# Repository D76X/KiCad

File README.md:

# KiCad: ESP32 IoT 4-layer PCB

[KiCad 9: Design & assemble an ESP32 IoT 4-layer PCB loaded with goodies **A Complete Guide** Tech Explorations](https://www.youtube.com/watch?v=LO9AO0XTX3M)  

[Peter Dalmaris futureshocked : KLP-5e-ESP32-sensor-board](https://github.com/futureshocked/KLP-5e-ESP32-sensor-board)  

## Suggested Routing Plan for a 4-layer board

1. Copper zones for GND
2. Copper zones for power
3. Differential pairs
4. Clock and high-speed signals
5. Power traces
6. All other signals
7. Optimization

---

## Parts

[SS-52400-002 Stewart Connector USB Type-C Connector | USB 3.1 | 1 Port | Right Angle Receptacle | Shielded | 0.039 in (1.00mm) PCB Thickness](https://www.snapeda.com/parts/SS-52400-002/Stewart%20Connector/view-part/?ref=search&t=SS-52400-002&ab_test_case=b)  

[MCP73871-2CAI/ML Microchip MCP73871-2CAI/ML, Battery Charge Controller, 1000mA, 20-Pin QFN | Microchip Technology Inc. MCP73871-2CAI/ML](https://www.snapeda.com/parts/MCP73871-2CAI/ML/Microchip/view-part/?ref=search&t=MCP7387-&ab_test_case=b)  

[LM1117MPX-3.3 800-mA 15-V linear voltage regulator](https://www.snapeda.com/parts/LM1117MPX-3.3/Texas%20Instruments/view-part/?ref=search&t=LM1117MPX-3.3&ab_test_case=b)  

[B2B-PH-SM4-TB Connector Header Surface Mount 2 position 0.079" (2.00mm)](https://www.snapeda.com/parts/B2B-PH-SM4-TB/JST/view-part/?ref=search&t=B2B&ab_test_case=b)  

---

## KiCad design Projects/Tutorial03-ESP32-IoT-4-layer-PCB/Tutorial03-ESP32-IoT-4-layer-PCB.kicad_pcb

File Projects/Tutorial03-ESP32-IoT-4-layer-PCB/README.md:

# KiCad

LED6
footprint: Project-Footprints:LEDC2012X120N

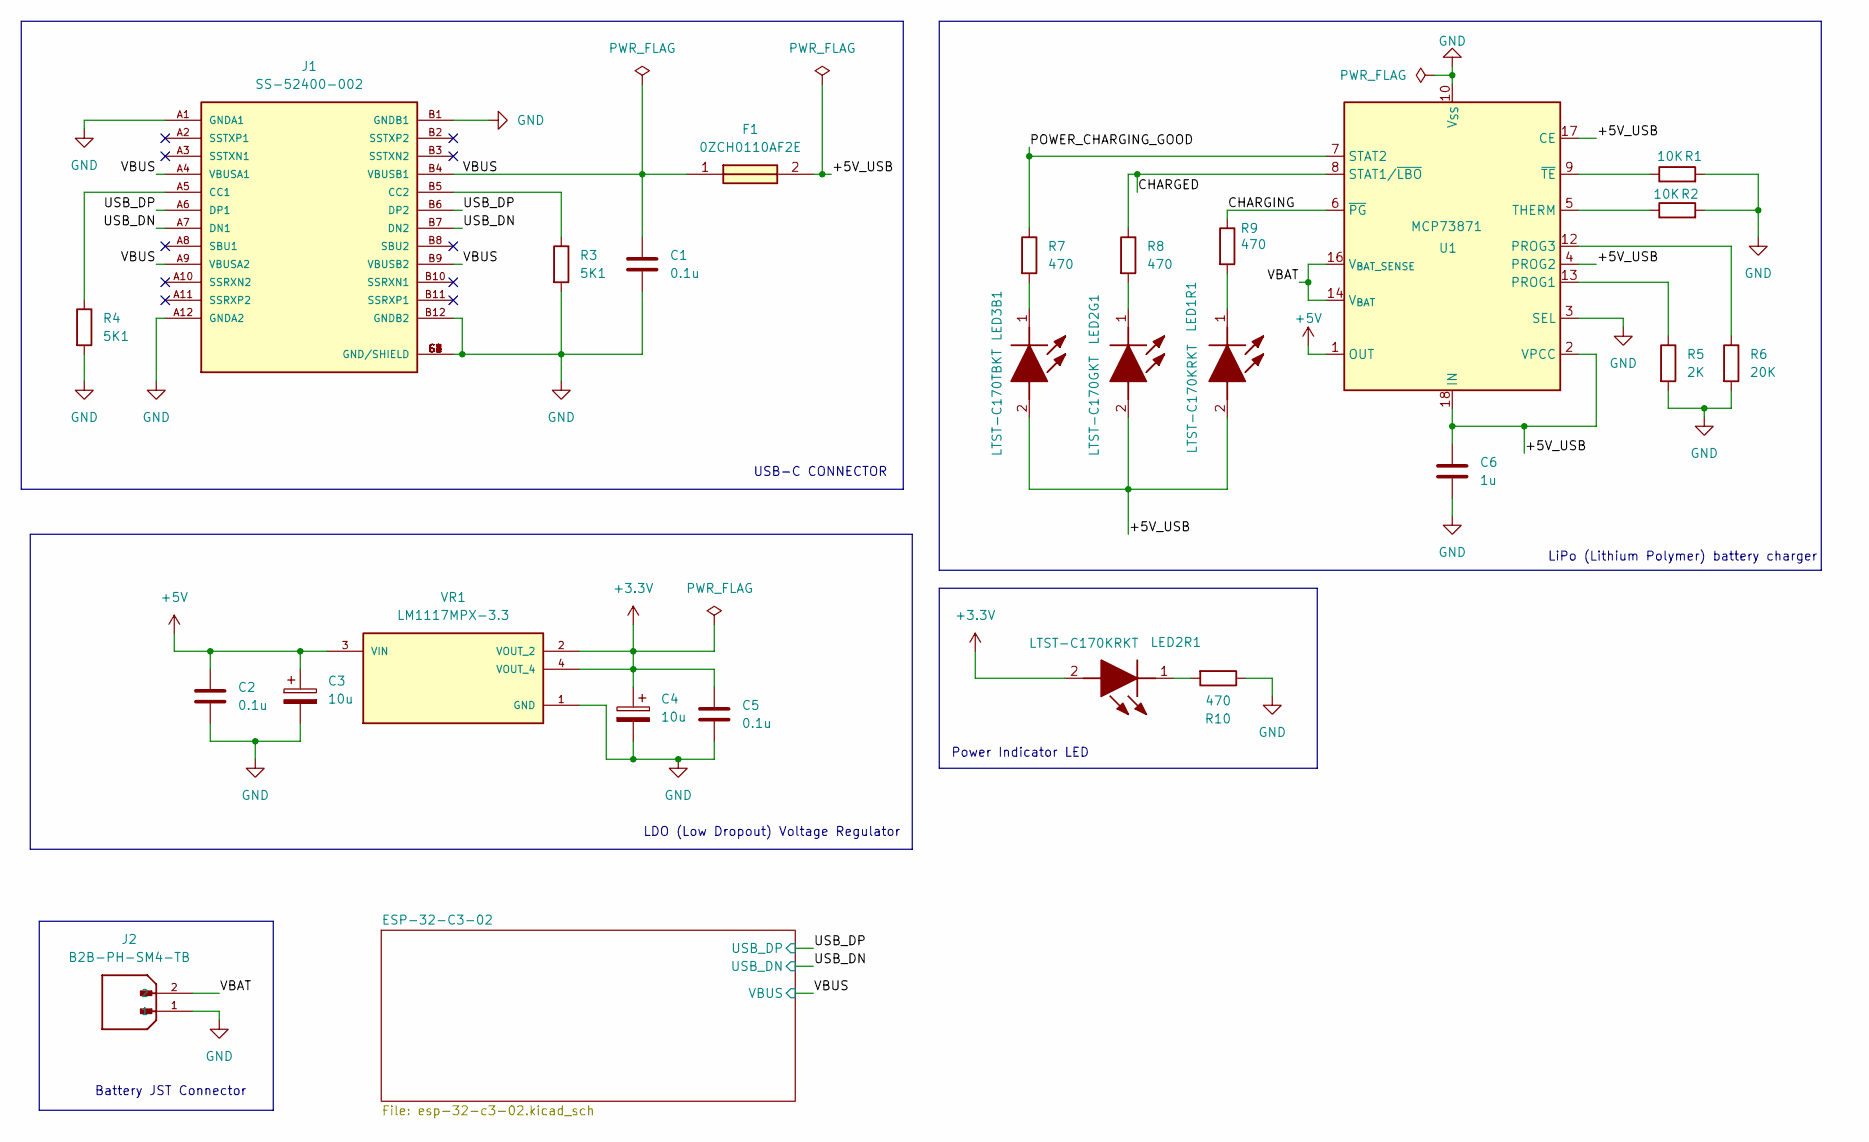
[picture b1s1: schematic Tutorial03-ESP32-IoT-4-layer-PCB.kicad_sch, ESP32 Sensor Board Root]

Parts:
C1, C2, C5: 0.1u; C_0805_2012Metric
C3, C4: 10u; T491A
C6: 1u; C_0805_2012Metric
F1: 0ZCH0110AF2E; FUSC3226X100N; Manufacturer_Part_Number 0ZCH0110AF2E
J1: SS-52400-002; BELFUSE_SS-52400-002; PARTREV A0
J2: B2B-PH-SM4-TB; JST_B2B-PH-SM4-TB; PARTREV N/A
LED1R1, LED2R1: LTST-C170KRKT; LEDC2012X120N; Manufacturer_Part_Number LTST-C170KRKT; Mouser Part Number 859-LTST-C170KRKT
LED2G1: LTST-C170GKT; LEDC2012X120N; Manufacturer_Part_Number LTST-C170GKT; Mouser Part Number 859-LTST-C170GKT
LED3B1: LTST-C170TBKT; LEDC2012X120N; Manufacturer_Part_Number LTST-C170TBKT; Mouser Part Number 859-LTST-C170TBKT
R1, R2: 10K; R_0805_2012Metric
R3, R4: 5K1; R_0805_2012Metric
R5: 2K; R_0805_2012Metric
R6: 20K; R_0805_2012Metric
R7, R8, R9, R10: 470; R_0805_2012Metric
U1: MCP73871; QFN-20-1EP_4x4mm_P0.5mm_EP2.5x2.5mm
VR1: LM1117MPX-3.3; VREG_LM1117MPX-3.3

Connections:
+3.3V: C4.1, C5.1, LED2R1.2 (A), VR1.2 (VOUT_2), VR1.4 (VOUT_4); also elsewhere on the board
+5V: C2.1, C3.1, U1.1 (OUT), U1.20 (OUT), VR1.3 (VIN)
/+5V_USB: C6.1, F1.2, LED1R1.2 (A), LED2G1.2 (A), LED3B1.2 (A), U1.2 (VPCC), U1.4 (PROG2), U1.17 (CE), U1.18 (IN), U1.19 (IN)
/CHARGED: R8.1, U1.8 (STAT1/~LBO)
/CHARGING: R9.1, U1.6 (~PG)
/POWER_CHARGING_GOOD: R7.1, U1.7 (STAT2)
/USB_DN: J1.A7 (DN1), J1.B7 (DN2); also elsewhere on the board
/USB_DP: J1.A6 (DP1), J1.B6 (DP2); also elsewhere on the board
/VBAT: J2.2, U1.14 (V_{BAT}), U1.15 (V_{BAT}), U1.16 (V_{BAT_SENSE})
/VBUS: C1.1, F1.1, J1.A4 (VBUSA1), J1.A9 (VBUSA2), J1.B4 (VBUSB1), J1.B9 (VBUSB2); also elsewhere on the board
GND: C1.2, C2.2, C3.2, C4.2, C5.2, C6.2, J1.A1 (GNDA1), J1.A12 (GNDA2), J1.B1 (GNDB1), J1.B12 (GNDB2), J1.G1 (GND/SHIELD), J1.G2 (GND/SHIELD), J1.G3 (GND/SHIELD), J1.G4 (GND/SHIELD), J1.S1 (GND/SHIELD), J1.S2 (GND/SHIELD), J1.S3 (GND/SHIELD), J1.S4 (GND/SHIELD), J2.1, R1.2, R2.2, R3.2, R4.2, R5.2, R6.2, R10.1, U1.3 (SEL), U1.10 (V_{SS}), U1.11 (V_{SS}), U1.21 (V_{SS}), VR1.1 (GND); also elsewhere on the board
unnamed: J1.A5 (CC1), R4.1
unnamed: J1.B5 (CC2), R3.1
unnamed: LED1R1.1 (K), R9.2
unnamed: LED2G1.1 (K), R8.2
unnamed: LED2R1.1 (K), R10.2
unnamed: LED3B1.1 (K), R7.2
unnamed: R5.1, U1.13 (PROG1)
unnamed: R6.1, U1.12 (PROG3)
unnamed: R2.1, U1.5 (THERM)
unnamed: R1.1, U1.9 (~TE)

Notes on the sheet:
USB-C CONNECTOR
Power Indicator LED
LiPo (Lithium Polymer) battery charger
LDO (Low Dropout) Voltage Regulator
Battery JST Connector

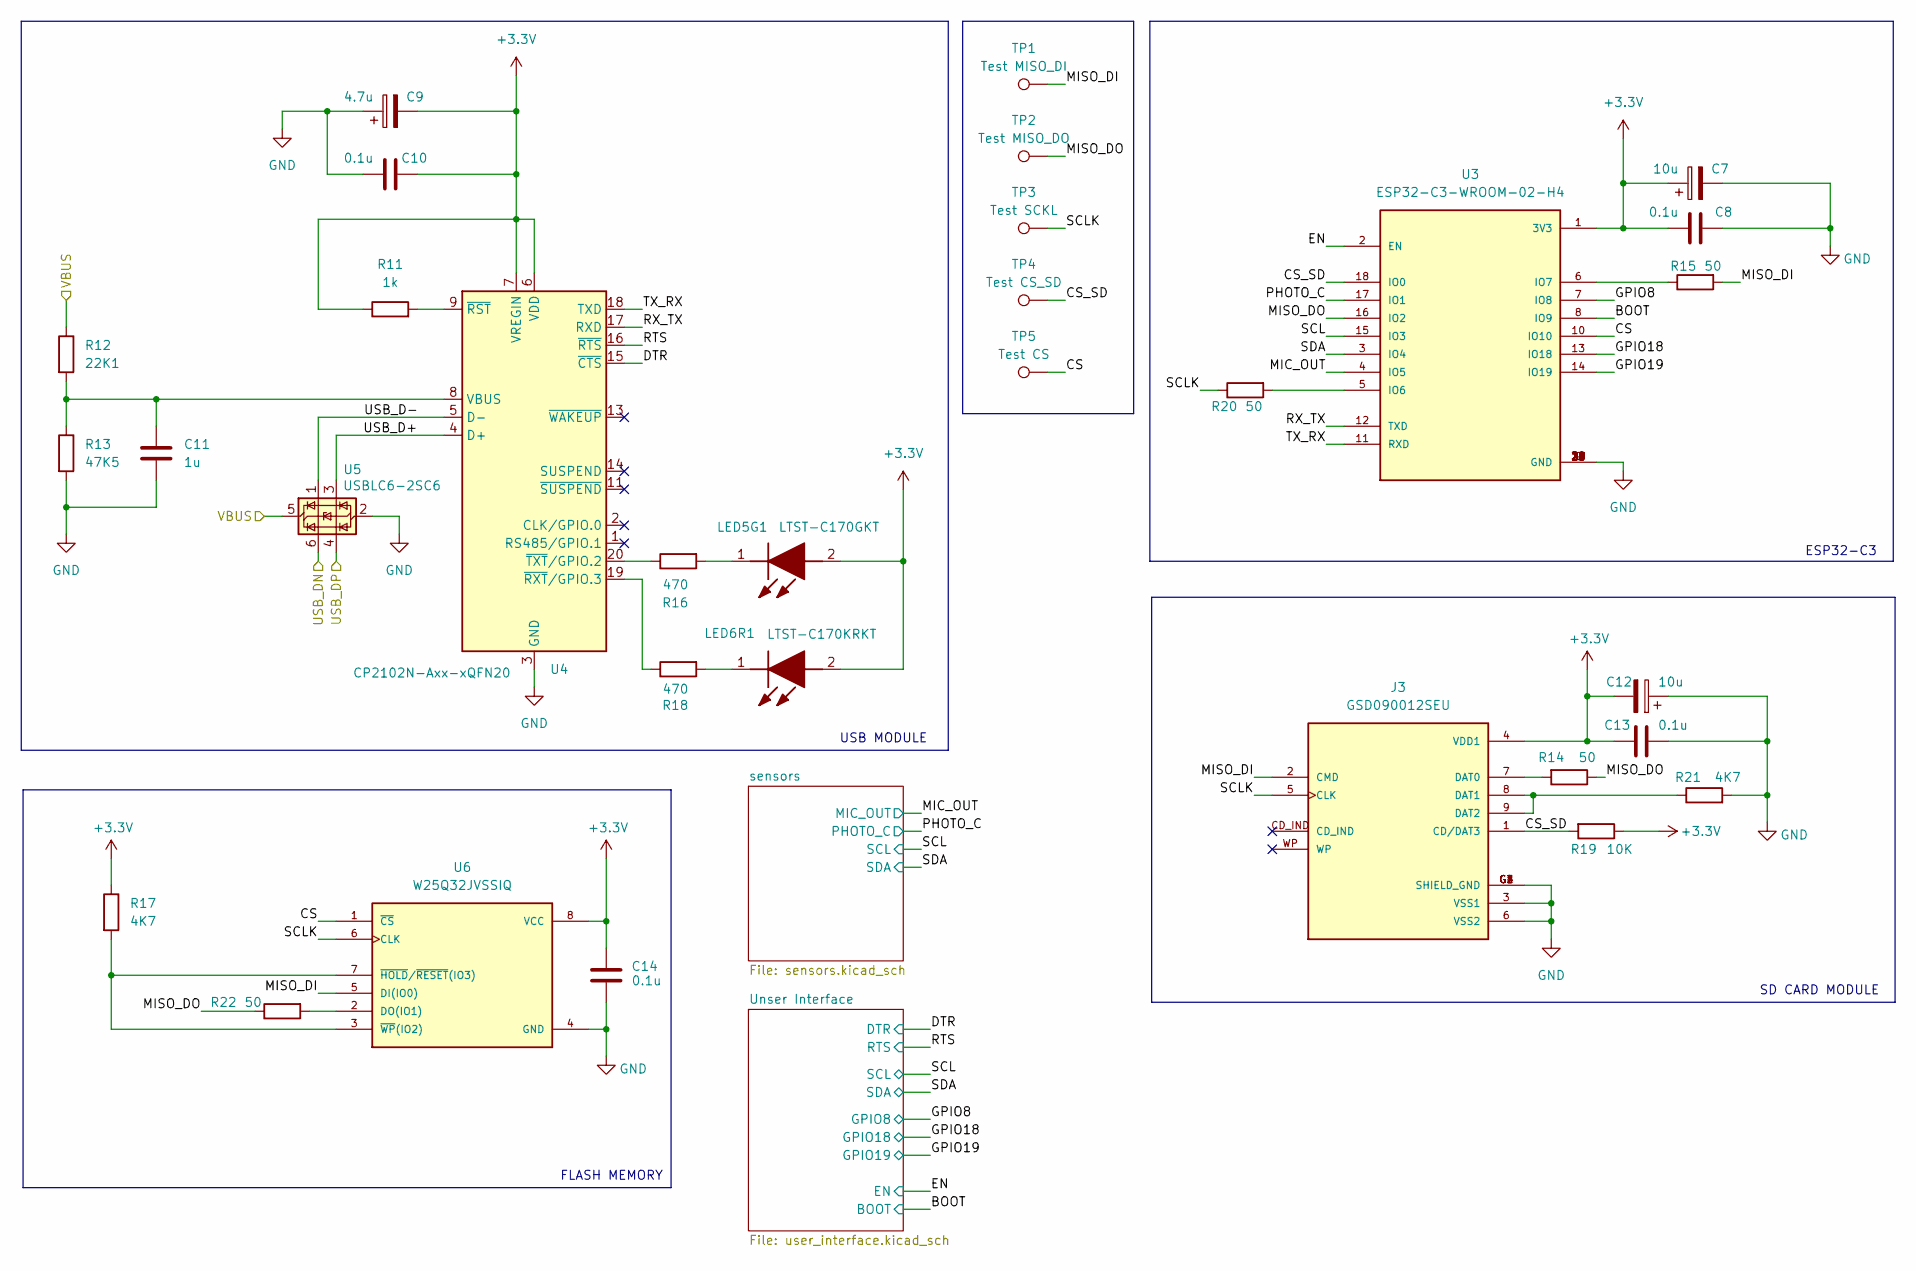
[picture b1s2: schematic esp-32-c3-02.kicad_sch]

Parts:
C7, C12: 10u; T491A
C8, C10, C13, C14: 0.1u; C_0805_2012Metric
C9: 4.7u; T491A
C11: 1u; C_0805_2012Metric
J3: GSD090012SEU; AMPHENOL_GSD090012SEU; PARTREV E
LED5G1: LTST-C170GKT; LEDC2012X120N; Manufacturer_Part_Number LTST-C170GKT; Mouser Part Number 859-LTST-C170GKT
LED6R1: LTST-C170KRKT; LEDC2012X120N; Manufacturer_Part_Number LTST-C170KRKT; Mouser Part Number 859-LTST-C170KRKT
R11: 1k; R_0805_2012Metric
R12: 22K1; R_0805_2012Metric
R13: 47K5; R_0805_2012Metric
R14, R15, R20, R22: 50; R_0805_2012Metric
R16, R18: 470; R_0805_2012Metric
R17, R21: 4K7; R_0805_2012Metric
R19: 10K; R_0805_2012Metric
TP1: Test MISO_DI; TestPoint_Pad_D1.0mm
TP2: Test MISO_DO; TestPoint_Pad_D1.0mm
TP3: Test SCKL; TestPoint_Pad_D1.0mm
TP4: Test CS_SD; TestPoint_Pad_D1.0mm
TP5: Test CS; TestPoint_Pad_D1.0mm
U3: ESP32-C3-WROOM-02-H4; MODULE_ESP32-C3-WROOM-02-H4
U4: CP2102N-Axx-xQFN20; QFN-20_L3.0-W3.0-P0.50-BL-EP1.7_EFM8BB21F16G
U5: USBLC6-2SC6; SOT-23-6
U6: W25Q32JVSSIQ; WSON-8-1EP_6x5mm_P1.27mm_EP3.4x4.3mm; M_PART_NUMBER W25QXX

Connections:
+3.3V: C7.1, C8.1, C9.2, C10.2, C12.2, C13.2, C14.1, J3.4 (VDD1), LED5G1.2 (A), LED6R1.2 (A), R11.1, R17.1, R19.1, U3.1 (3V3), U4.6 (VDD), U4.7 (VREGIN), U6.8 (VCC); also elsewhere on the board
/ESP-32-C3-02/BOOT: U3.8 (IO9); also elsewhere on the board
/ESP-32-C3-02/CS: TP5.1 (1_1), U3.10 (IO10), U6.1 (~CS)
/ESP-32-C3-02/CS_SD: J3.1 (CD/DAT3), R19.2, TP4.1 (1_1), U3.18 (IO0)
/ESP-32-C3-02/DTR: U4.15 (~CTS); also elsewhere on the board
/ESP-32-C3-02/EN: U3.2 (EN); also elsewhere on the board
/ESP-32-C3-02/GPIO8: U3.7 (IO8); also elsewhere on the board
/ESP-32-C3-02/GPIO18: U3.13 (IO18); also elsewhere on the board
/ESP-32-C3-02/GPIO19: U3.14 (IO19); also elsewhere on the board
/ESP-32-C3-02/MIC_OUT: U3.4 (IO5); also elsewhere on the board
/ESP-32-C3-02/MISO_DI: J3.2 (CMD), R15.2, TP1.1 (1_1), U6.5 (DI(IO0))
/ESP-32-C3-02/MISO_DO: R14.1, R22.1, TP2.1 (1_1), U3.16 (IO2)
/ESP-32-C3-02/PHOTO_C: U3.17 (IO1); also elsewhere on the board
/ESP-32-C3-02/RTS: U4.16 (~RTS); also elsewhere on the board
/ESP-32-C3-02/RX_TX: U3.12 (TXD), U4.17 (RXD)
/ESP-32-C3-02/SCL: U3.15 (IO3); also elsewhere on the board
/ESP-32-C3-02/SCLK: J3.5 (CLK), R20.1, TP3.1 (1_1), U6.6 (CLK)
/ESP-32-C3-02/SDA: U3.3 (IO4); also elsewhere on the board
/ESP-32-C3-02/TX_RX: U3.11 (RXD), U4.18 (TXD)
/ESP-32-C3-02/USB_D+: U4.4 (D+), U5.3 (I/O2)
/ESP-32-C3-02/USB_D-: U4.5 (D-), U5.1 (I/O1)
/USB_DN: U5.6 (I/O1); also elsewhere on the board
/USB_DP: U5.4 (I/O2); also elsewhere on the board
/VBUS: R12.1, U5.5 (VBUS); also elsewhere on the board
GND: C7.2, C8.2, C9.1, C10.1, C11.2, C12.1, C13.1, C14.2, J3.3 (VSS1), J3.6 (VSS2), J3.G1 (SHIELD_GND), J3.G2 (SHIELD_GND), J3.G3 (SHIELD_GND), J3.G4 (SHIELD_GND), R13.2, R21.2, U3.9 (GND), U3.19 (GND), U3.20 (GND), U3.21 (GND), U3.22 (GND), U3.23 (GND), U3.24 (GND), U3.25 (GND), U3.26 (GND), U3.27 (GND), U3.28 (GND), U3.29 (GND), U3.30 (GND), U3.31 (GND), U3.32 (GND), U3.33 (GND), U3.34 (GND), U3.35 (GND), U3.36 (GND), U3.37 (GND), U3.38 (GND), U3.39 (GND), U4.3 (GND), U4.12 (GND), U4.21 (GND), U5.2 (GND), U6.4 (GND); also elsewhere on the board
unnamed: J3.7 (DAT0), R14.2
unnamed: J3.8 (DAT1), J3.9 (DAT2), R21.1
unnamed: LED5G1.1 (K), R16.2
unnamed: LED6R1.1 (K), R18.2
unnamed: R20.2, U3.5 (IO6)
unnamed: R15.1, U3.6 (IO7)
unnamed: C11.1, R12.2, R13.1, U4.8 (VBUS)
unnamed: R11.2, U4.9 (~RST)
unnamed: R18.1, U4.19 (~RXT/GPIO.3)
unnamed: R16.1, U4.20 (~TXT/GPIO.2)
unnamed: R22.2, U6.2 (DO(IO1))
unnamed: R17.2, U6.3 (~WP(IO2)), U6.7 (~HOLD/~RESET(IO3))

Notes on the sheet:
ESP32-C3
SD CARD MODULE
FLASH MEMORY
USB MODULE

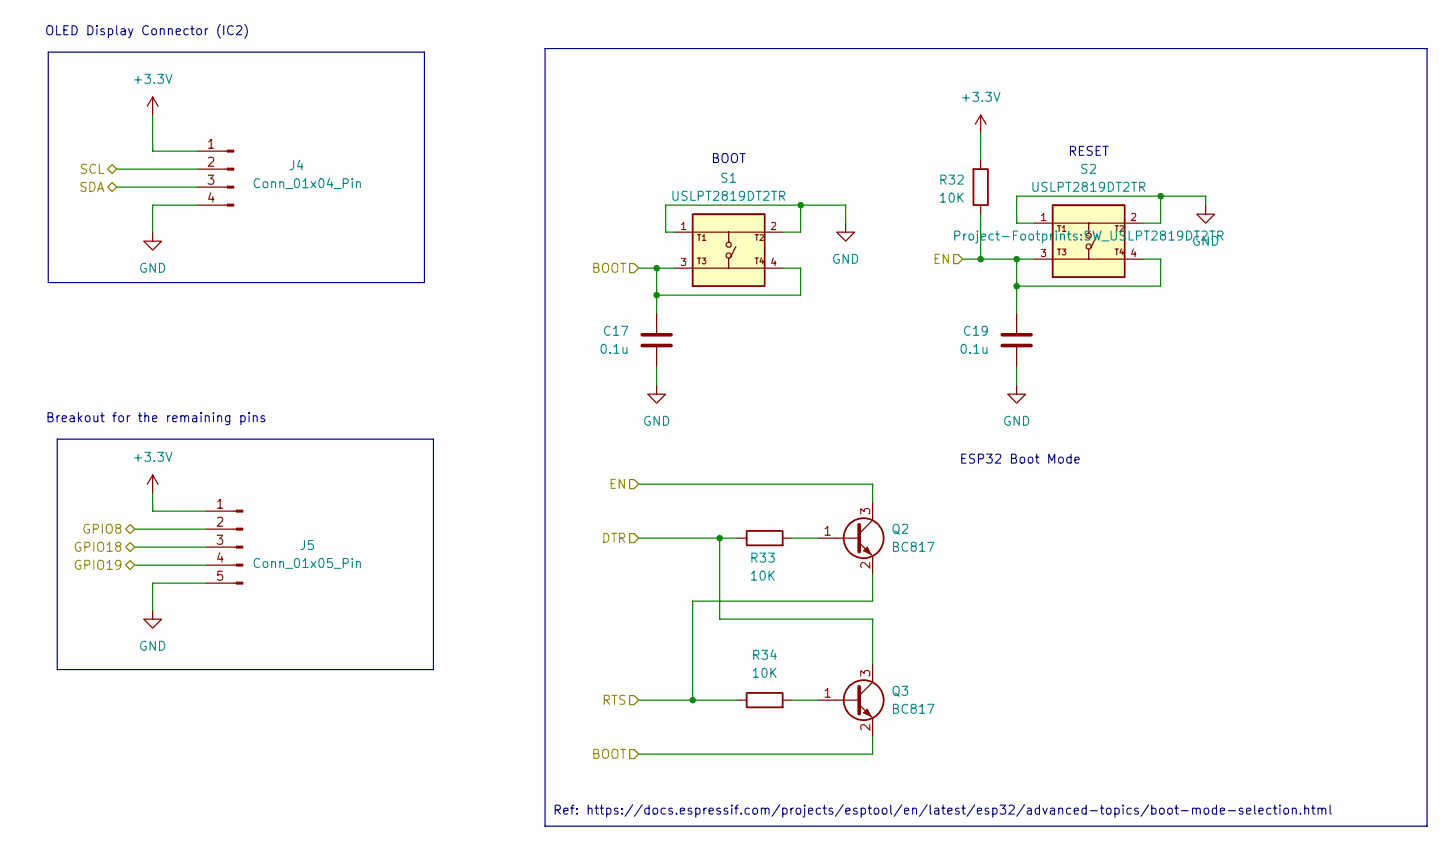
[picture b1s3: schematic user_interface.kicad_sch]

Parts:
C17, C19: 0.1u; C_0805_2012Metric
J4: Conn_01x04_Pin; PinHeader_1x04_P2.54mm_Vertical
J5: Conn_01x05_Pin; PinHeader_1x05_P2.54mm_Vertical
Q2, Q3: BC817; SOT-23
R32, R33, R34: 10K; R_0805_2012Metric
S1, S2: USLPT2819DT2TR; SW_USLPT2819DT2TR; PARTREV P

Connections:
+3.3V: J4.1, J5.1, R32.2; also elsewhere on the board
/ESP-32-C3-02/BOOT: C17.1, Q3.2 (E), S1.3, S1.4; also elsewhere on the board
/ESP-32-C3-02/DTR: Q3.3 (C), R33.1; also elsewhere on the board
/ESP-32-C3-02/EN: C19.1, Q2.3 (C), R32.1, S2.3, S2.4; also elsewhere on the board
/ESP-32-C3-02/GPIO8: J5.2; also elsewhere on the board
/ESP-32-C3-02/GPIO18: J5.3; also elsewhere on the board
/ESP-32-C3-02/GPIO19: J5.4; also elsewhere on the board
/ESP-32-C3-02/RTS: Q2.2 (E), R34.1; also elsewhere on the board
/ESP-32-C3-02/SCL: J4.2; also elsewhere on the board
/ESP-32-C3-02/SDA: J4.3; also elsewhere on the board
GND: C17.2, C19.2, J4.4, J5.5, S1.1, S1.2, S2.1, S2.2; also elsewhere on the board
unnamed: Q2.1 (B), R33.2
unnamed: Q3.1 (B), R34.2

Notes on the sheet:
Ref: https://docs.espressif.com/projects/esptool/en/latest/esp32/advanced-topics/boot-mode-selection.html
RESET
Breakout for the remaining pins
BOOT
OLED Display Connector (IC2)
ESP32 Boot Mode

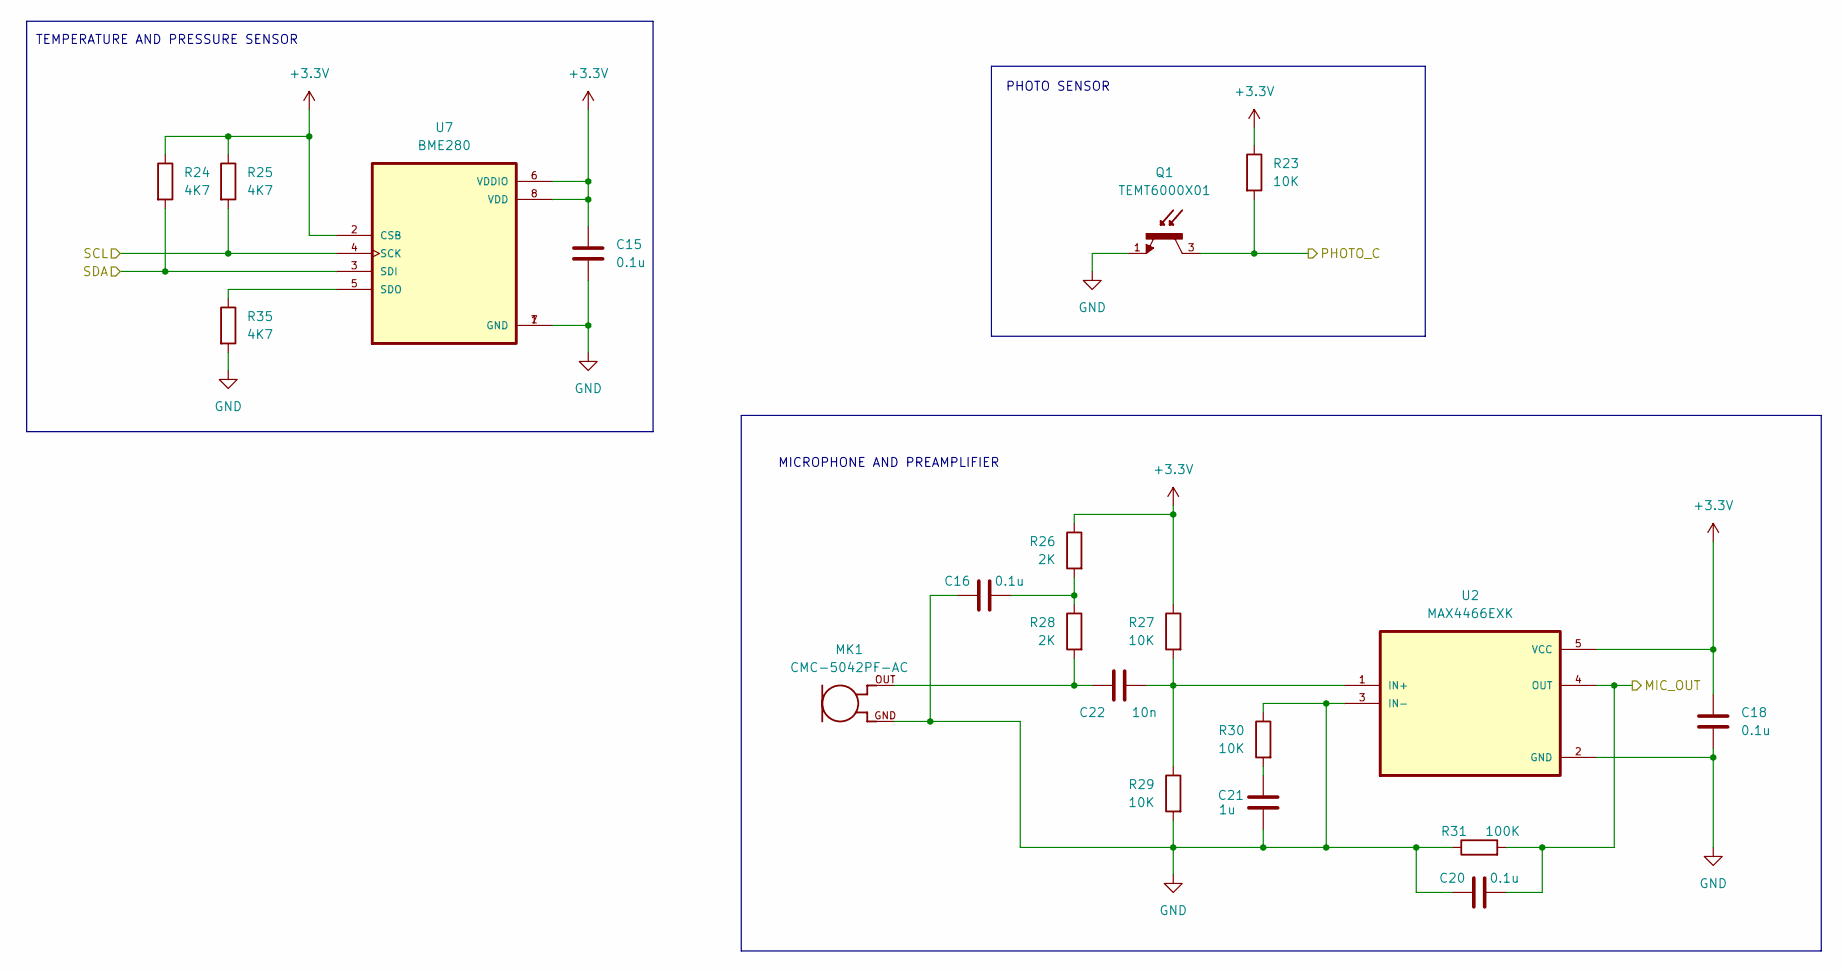
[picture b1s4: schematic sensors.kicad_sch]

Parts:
C15, C16, C18, C20: 0.1u; C_0805_2012Metric
C21: 1u; C_0805_2012Metric
C22: 10n; C_0805_2012Metric
MK1: CMC-5042PF-AC; CUI_CMC-5042PF-AC
Q1: TEMT6000X01; TRANS_TEMT6000X01; PARTREV 1.9
R23, R27, R29, R30: 10K; R_0805_2012Metric
R24, R25, R35: 4K7; R_0805_2012Metric
R26, R28: 2K; R_0805_2012Metric
R31: 100K; R_0805_2012Metric
U2: MAX4466EXK; SOT65P210X110-5N
U7: BME280; PSON65P250X250X100-8N

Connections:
+3.3V: C15.1, C18.1, R23.1, R24.1, R25.1, R26.1, R27.1, U2.5 (VCC), U7.2 (CSB), U7.6 (VDDIO), U7.8 (VDD); also elsewhere on the board
/ESP-32-C3-02/MIC_OUT: C20.2, R31.2, U2.4 (OUT); also elsewhere on the board
/ESP-32-C3-02/PHOTO_C: Q1.3, R23.2; also elsewhere on the board
/ESP-32-C3-02/SCL: R25.2, U7.4 (SCK); also elsewhere on the board
/ESP-32-C3-02/SDA: R24.2, U7.3 (SDI); also elsewhere on the board
GND: C15.2, C16.1, C18.2, C20.1, C21.2, MK1.GND, Q1.1, R29.2, R30.1, R31.1, R35.2, U2.2 (GND), U2.3 (IN-), U7.1 (GND), U7.7 (GND); also elsewhere on the board
unnamed: C16.2, R26.2, R28.1
unnamed: C21.1, R30.2
unnamed: C22.1, MK1.OUT, R28.2
unnamed: C22.2, R27.2, R29.1, U2.1 (IN+)
unnamed: R35.1, U7.5 (SDO)

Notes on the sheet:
MICROPHONE AND PREAMPLIFIER
TEMPERATURE AND PRESSURE SENSOR
PHOTO SENSOR

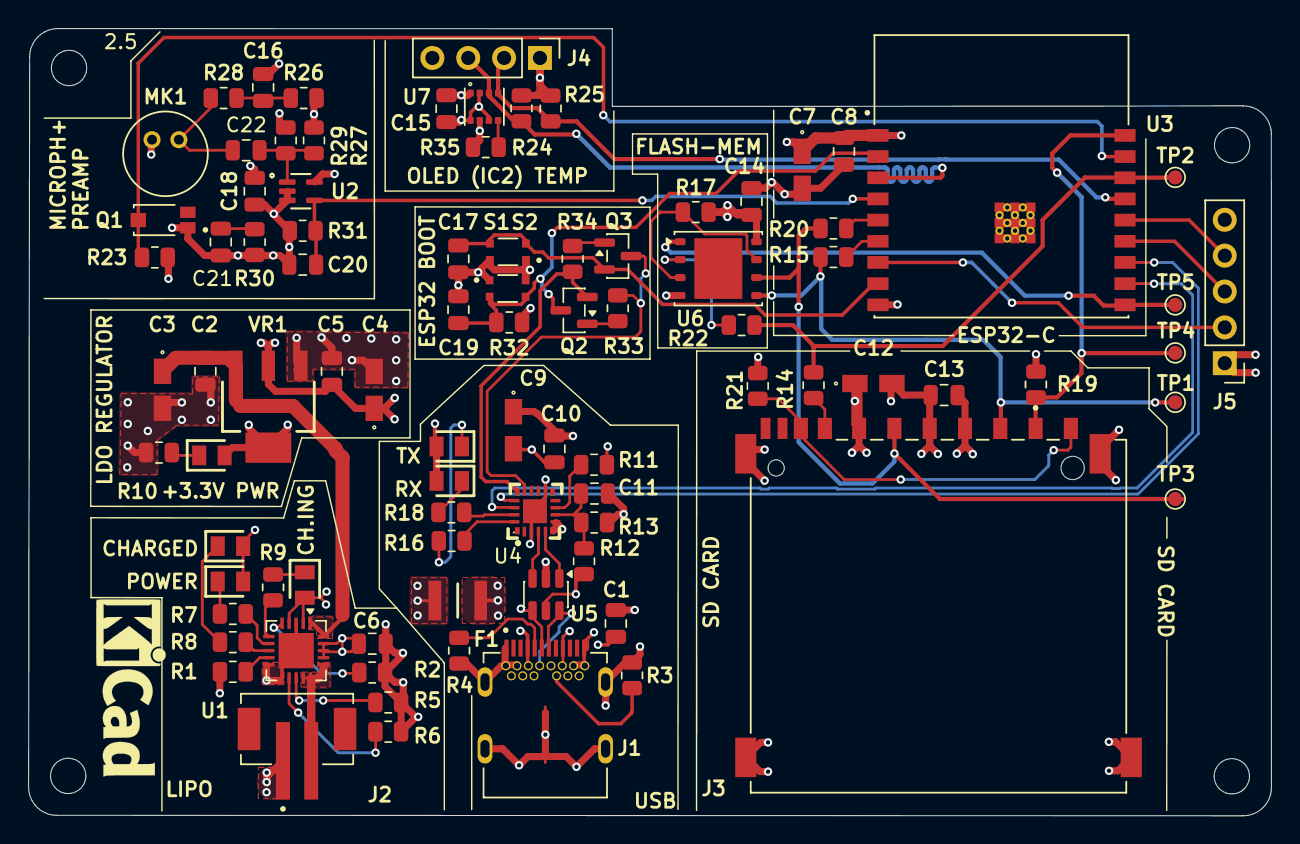
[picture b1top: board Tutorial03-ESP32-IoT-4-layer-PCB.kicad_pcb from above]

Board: 4 copper layers, 88.0 x 55.8 mm, 91 parts (0 on the bottom side), 60 nets.

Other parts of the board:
2.5, 2.5#2, 2.5#3: MountingHole_2.5mm

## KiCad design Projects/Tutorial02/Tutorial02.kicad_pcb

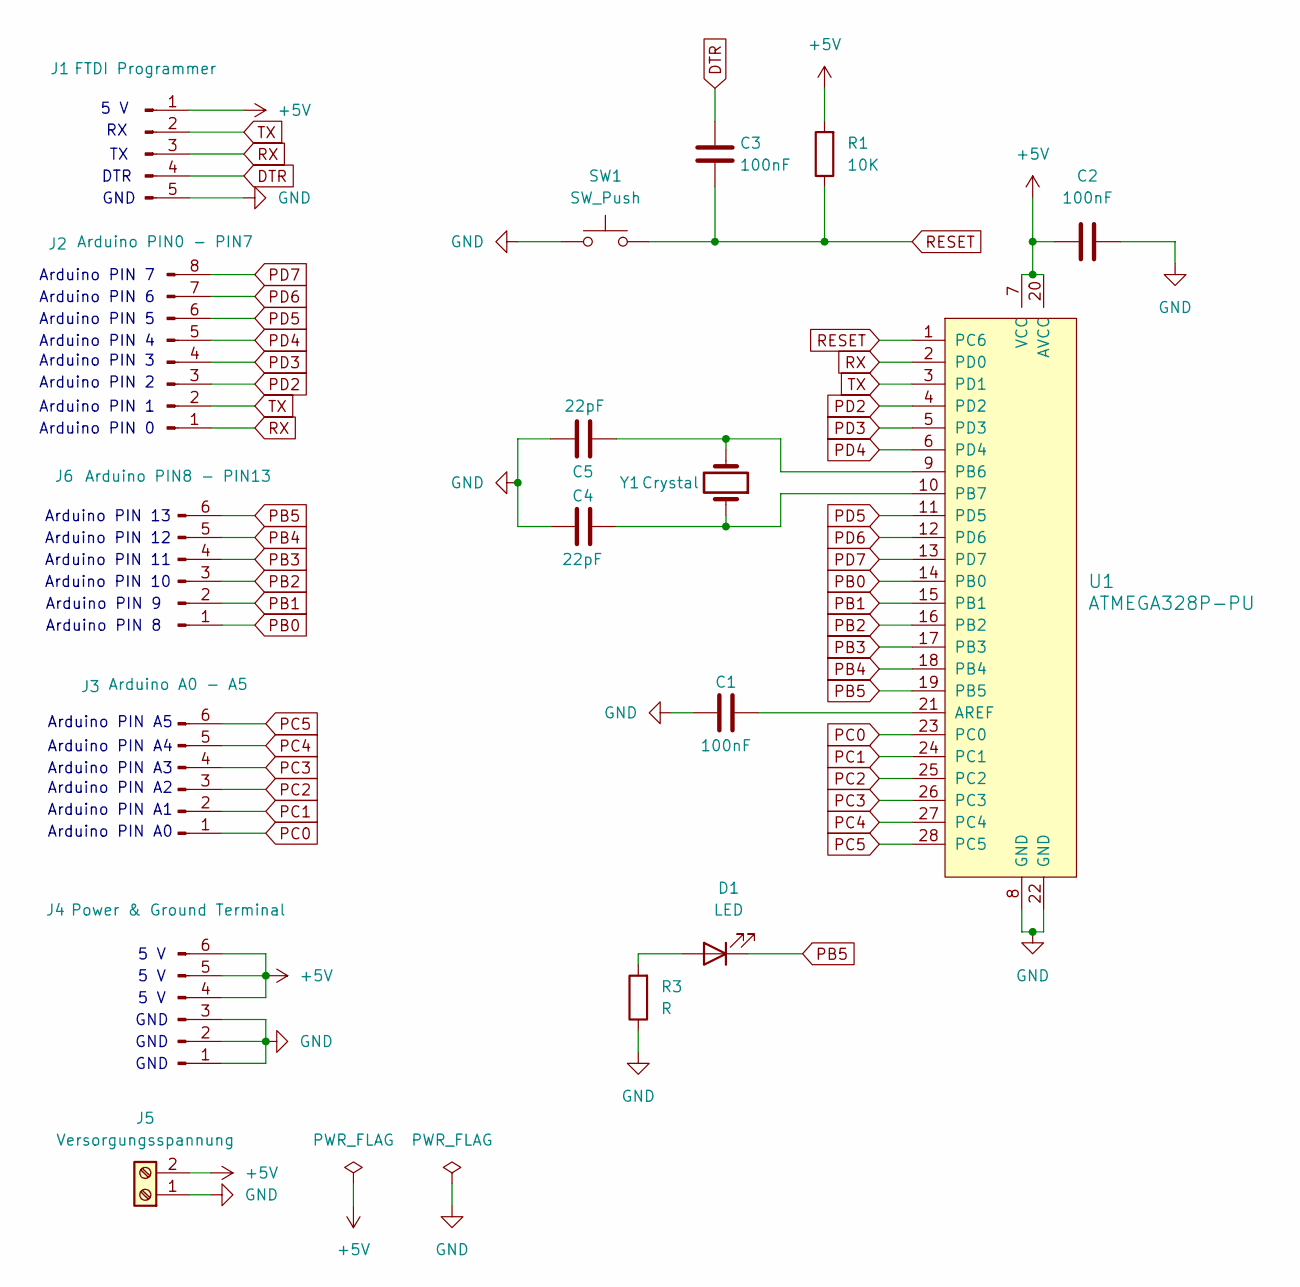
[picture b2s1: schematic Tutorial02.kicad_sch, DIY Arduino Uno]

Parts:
C1, C2, C3: 100nF; C_Disc_D6.0mm_W2.5mm_P5.00mm
C4, C5: 22pF; C_Disc_D3.8mm_W2.6mm_P2.50mm
D1: LED; LED_D5.0mm
J1: FTDI Programmer; PinHeader_1x05_P2.54mm_Vertical
J2: Arduino PIN0 - PIN7; PinHeader_1x08_P2.54mm_Vertical
J3: Arduino A0 - A5; PinHeader_1x06_P2.54mm_Vertical
J4: Power & Ground Terminal; PinHeader_1x06_P2.54mm_Vertical
J5: Versorgungsspannung; TerminalBlock_TE_282834-2_1x02_P2.54mm_Horizontal
J6: Arduino PIN8 - PIN13; PinHeader_1x06_P2.54mm_Vertical
R1: 10K; R_Axial_DIN0204_L3.6mm_D1.6mm_P7.62mm_Horizontal
R3: R; R_Axial_DIN0204_L3.6mm_D1.6mm_P7.62mm_Horizontal
SW1: SW_Push; SW_PUSH_6mm_H7.3mm
U1: ATMEGA328P-PU; DIP-28_W7.62mm; MPN ATMEGA328P-PU; Digi-Key_PN ATMEGA328P-PU-ND
Y1: Crystal; Crystal_HC52-6mm_Vertical

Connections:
+5V: C2.1, J1.1, J4.4, J4.5, J4.6, J5.2, R1.2, U1.7 (VCC), U1.20 (AVCC)
DTR: C3.1, J1.4
GND: C1.1, C2.2, C4.1, C5.1, J1.5, J4.1, J4.2, J4.3, J5.1, R3.1, SW1.1, U1.8 (GND), U1.22 (GND)
unnamed: D1.2 (A), R3.2
unnamed: C1.2, U1.21 (AREF)
unnamed: C5.2, U1.9 (PB6), Y1.2
unnamed: C4.2, U1.10 (PB7), Y1.1
PB0: J6.1, U1.14 (PB0)
PB1: J6.2, U1.15 (PB1)
PB2: J6.3, U1.16 (PB2)
PB3: J6.4, U1.17 (PB3)
PB4: J6.5, U1.18 (PB4)
PB5: D1.1 (K), J6.6, U1.19 (PB5)
PC0: J3.1, U1.23 (PC0)
PC1: J3.2, U1.24 (PC1)
PC2: J3.3, U1.25 (PC2)
PC3: J3.4, U1.26 (PC3)
PC4: J3.5, U1.27 (PC4)
PC5: J3.6, U1.28 (PC5)
PD2: J2.3, U1.4 (PD2)
PD3: J2.4, U1.5 (PD3)
PD4: J2.5, U1.6 (PD4)
PD5: J2.6, U1.11 (PD5)
PD6: J2.7, U1.12 (PD6)
PD7: J2.8, U1.13 (PD7)
RESET: C3.2, R1.1, SW1.2, U1.1 (PC6)
RX: J1.3, J2.1, U1.2 (PD0)
TX: J1.2, J2.2, U1.3 (PD1)

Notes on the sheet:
Arduino PIN 9
GND
5 V
Arduino PIN 12
Arduino PIN 4
DTR
Arduino PIN A0
Arduino PIN A5
Arduino PIN A4
Arduino PIN A2
Arduino PIN 10
Arduino PIN 1
Arduino PIN 7
Arduino PIN 2
Arduino PIN 11
Arduino PIN 13
Arduino PIN A3
Arduino PIN 5
Arduino PIN 8
Arduino PIN 3
Arduino PIN 0
5 V
Arduino PIN 6
Arduino PIN A1

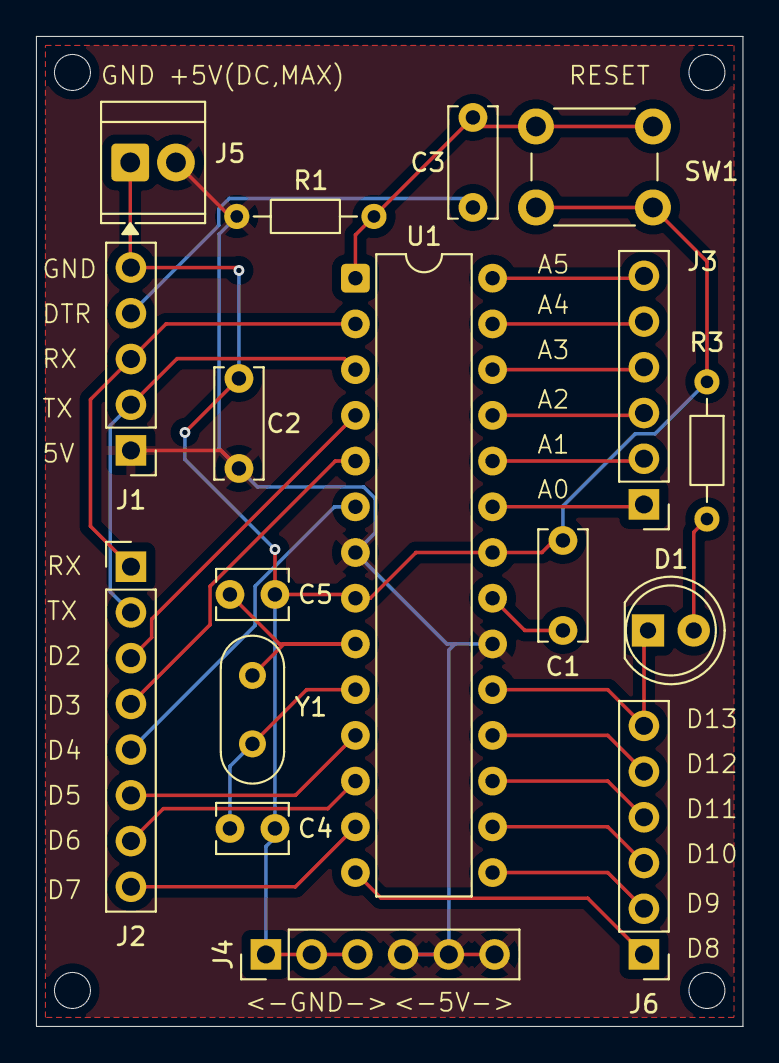
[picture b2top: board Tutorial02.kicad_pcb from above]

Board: 2 copper layers, 39.2 x 55.0 mm, 17 parts (0 on the bottom side), 28 nets.

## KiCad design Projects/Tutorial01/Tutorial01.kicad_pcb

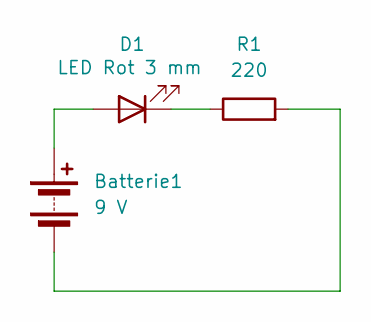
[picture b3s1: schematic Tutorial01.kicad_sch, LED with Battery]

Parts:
Batterie1: 9 V; BatteryHolder_Keystone_103_1x20mm
D1: LED Rot 3 mm; LED_D3.0mm
R1: 220; R_Axial_DIN0207_L6.3mm_D2.5mm_P10.16mm_Horizontal

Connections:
unnamed: Batterie1.1 (+), D1.2 (A)
unnamed: Batterie1.2 (-), R1.2
unnamed: D1.1 (K), R1.1

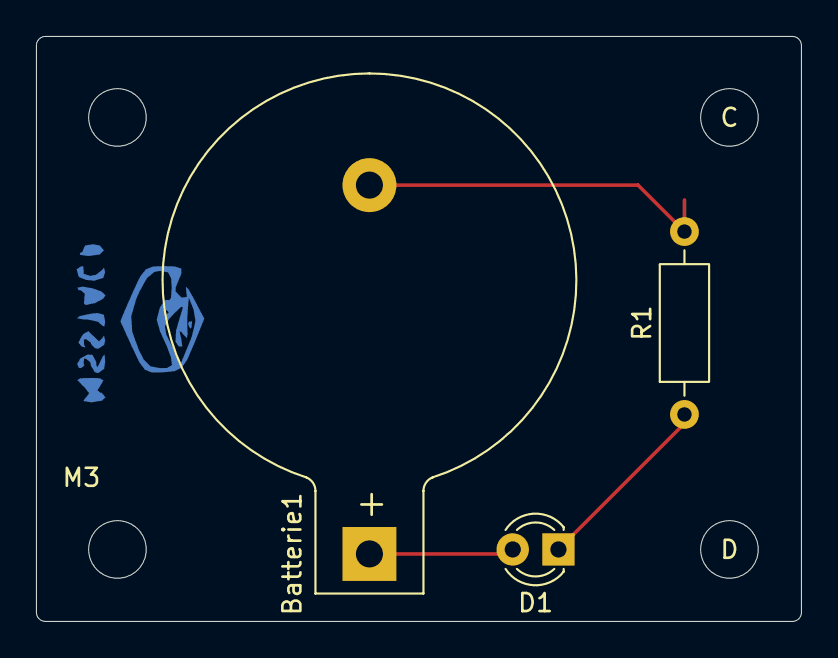
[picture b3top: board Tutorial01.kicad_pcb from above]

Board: 2 copper layers, 42.5 x 32.5 mm, 7 parts (0 on the bottom side), 3 nets.

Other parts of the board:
C: MountingHole_3.2mm_M3
D: MountingHole_3.2mm_M3
M3, M3#2: MountingHole_3.2mm_M3

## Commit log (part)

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2025-10-26 first commit Tutorial01 prj
2025-10-26 second commit
2025-10-26 LED with Battery schematic
2025-11-03 added R
2025-11-06 20251106 diode+battery
2025-11-08 20251108 diode+battery Anschluss
2025-11-08 20251108 Schaltplan mit Batterie 9V, eine rote Diode 3 mm Durchmnesser und ein Widerstand 220 ohm
2025-11-10 20251110 diode+battery referenze und ERC
2025-11-13 20251113 Schaltplan mit Batterie 9V, eine rote Diode 3 mm Durchmnesser und ein Widerstand 220 ohm
2025-11-14 20251114 Schaltplan mit Batterie 9V, eine rote Diode 3 mm Durchmnesser und ein Widerstand 220 ohm
2025-11-15 commit all
2025-11-15 20251115 Schaltplan mit Batterie 9V, eine rote Diode 3 mm Durchmnesser und ein Widerstand 220 ohm
2025-11-18 20251118 Schaltplan mit Batterie 9V, eine rote Diode 3 mm Durchmnesser und ein Widerstand 220 ohm
2025-11-19 20251119 Schaltplan mit Batterie 9V, eine rote Diode 3 mm Durchmnesser und ein Widerstand 220 ohm
2025-11-21 20251121 tutorial01
2025-11-27 20251127 Tutorial02 DIY Arduino Uno
2025-11-28 20251128 Tutorial02 DIY Arduino Uno
2025-11-29 202511219 tutorial02
2025-11-29 20251129 tutorial02
2025-12-02 20251202 Tutorial02 DIY Arduino Uno
2025-12-06 20251206 Tutorial02 DIY Arduino Uno
2025-12-06 20251206 tutorial02
2025-12-07 20251207 tutorial02
2025-12-08 20251212 tutorial02
2025-12-09 20251209 tutorial02
2025-12-10 20251210 tutorial02
2025-12-16 20251216 tutorial14
2025-12-17 20251217 tutorial14
2025-12-18 20251218-01 Tutorial14
2025-12-19 20251219-tutorial-14-01
2025-12-20 20251220-tutorial-14
2025-12-22 20251222-tutorial-15
2025-12-28 20251228
2025-12-29 20251229
2026-01-03 20260103
2026-01-04 20250104
2026-01-25 20260128
2026-01-31 20260131
2026-02-05 20260205
2026-02-07 20260207
2026-02-14 20260214
2026-02-20 20260220
2026-02-21 20260221
2026-03-01 20260301
2026-03-08 20260308
2026-03-15 20260315
2026-03-21 20260321
2026-03-28 20260329
2026-04-25 20260425
2026-05-01 20260501
2026-05-02 20260502
2026-05-16 20260516
2026-05-25 20260525
2026-05-30 20260530
2026-06-02 20260602
2026-06-06 20260606
2026-06-07 20260607
2026-06-13 20260513
2026-06-14 20260614
2026-06-20 20260620
2026-06-25 20260625
2026-06-26 20260626
2026-06-28 20260628
2026-06-30 20260630
